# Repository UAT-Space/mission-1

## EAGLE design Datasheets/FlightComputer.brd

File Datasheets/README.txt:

Flight Computer Module [By Kenneth Vorseth]
>>For UAT SPACE Program

FlightComputer.brd : Eagle Circuit Board File
FlightComputer.sch : Eagle Schematic (VERY USEFUL!)

Temperature Rating: -40C to 85C (CPU: -40C to 105C)

Microcontroller Pinout Connections
---------------------------------------------
AVR	|    Arduino	|	Usage       |
---------------------------------------------
PD0	|	0	| UART RX   (GPS/PC)|
PD1	|	1	| UART TX   (GPS/PC)|
PD2	|	2	| 1Hz Interrupt     |
PD3	|	3	| Servo A	    |
PD5	|	5	| Servo B	    |
PD6	|	6	| Servo C	    |
PD7	|	7	| SOFT RX (RADIO RX)|
PB0	|	8	| SOFT TX (RADIO TX)|
PB2	|	10	| SS   (ISP/SD CARD)|
PB3	|	11	| MOSI (ISP/SD CARD)|
PB4	|	12	| MISO (ISP/SD CARD)|
PB5	|	13	| SCK  (ISP/SD CARD)|
PC0	|	14/A0	| GPIO A	    |
PC1	|	15/A1	| GPIO B            |
PC2	|	16/A2	| GPIO C  	    |
PC4	|	18	| SDA       (BNO055)| 
PC5	|	19	| SCL	    (BNO055)|
---------------------------------------------

Usage Notes:
- Arduino Bootloader needs to be programmed via provided ISP header.
- When programming the device, use an FTDI cable attached to the designated pinout.
	-> Note that external power (VIN) must be supplied, and the PC must share GND.
	-> This means that you CANNNOT USE A LAPTOP BATTERY, PLUG IN LAPTOP.
- Power Supply (VIN) needs to be greater than 9 Volts.
- Do NOT power manually the 5V or 3.3V rails.
- The uBlox MAX8 GPS should interrupt the MCU once every second (1Hz).
	-> This can be used as an internal timekeeping method.
- The Micro SD Card is hooked up via SPI.
- The Inertial Measurement Unit (BNO055) is hooked up via I2C.
	-> The default address for the BNO055 is in the datasheet.
- Using the two jumpers, you can swap between using the UART with...
	-> Left Position:  UART TO GPS (For use in Field)
	-> Right Position: UART TO PC (FTDI for Programming/Serial Monitor)
- The RS-232 serial port is 12V tolerant, do NOT try to use 5V on this!

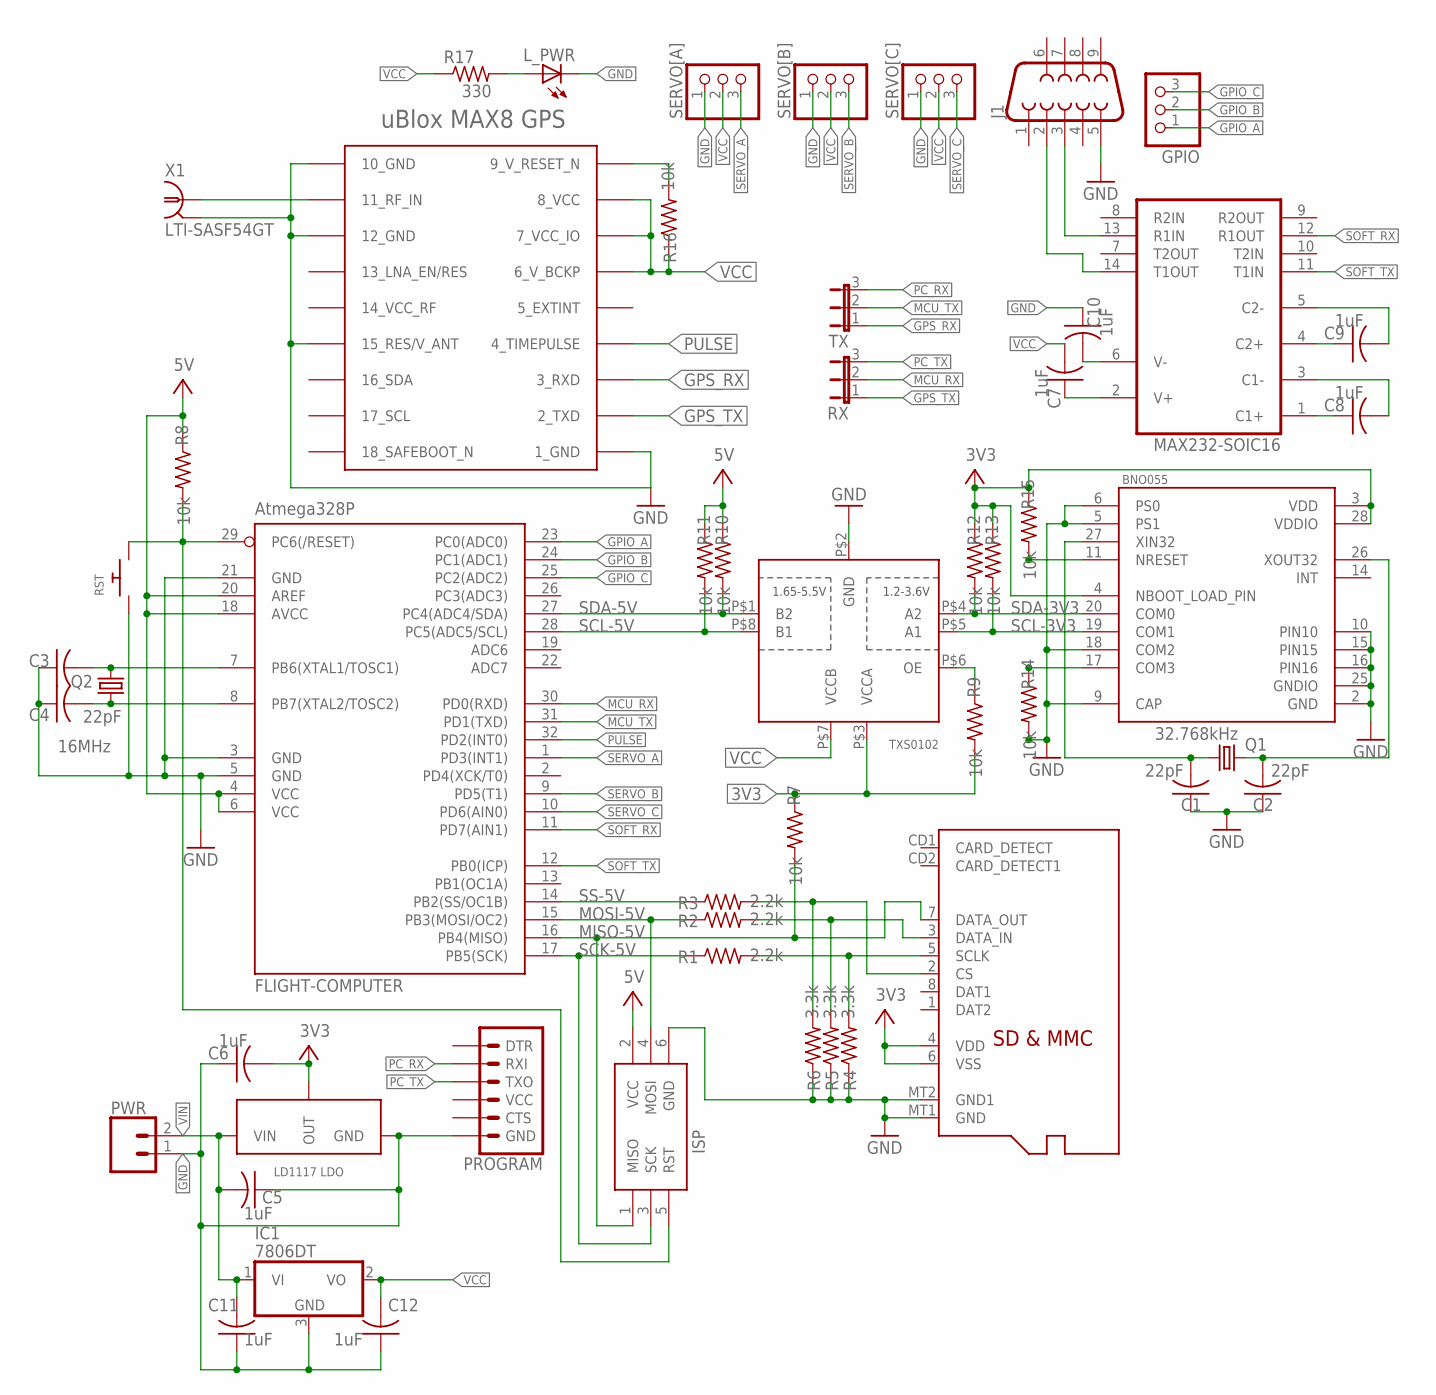
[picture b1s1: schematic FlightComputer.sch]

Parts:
BNO055: BNO055; LGA28R50P4X10_380X520X100
C1, C2, C3, C4: 22pF; C0805
C5, C6, C7, C8, C9, C10, C11, C12: 1uF; C0805
FLIGHT-COMPUTER: Atmega328P; TQFP32-08
GPIO: PINHD-1X3; 1X03
IC1: 7806DT; TO252
ISP: AVRISP-BOX
J1: DB9MALE; DB9_MALE
L_PWR: LEDSML0805; SML0805
MAX232-SOIC16: MAX232ECWE; SO16L
PROGRAM: 6_PIN_SERIAL_TARGETSILK; 6_PIN_SERIAL_TARGET_SIDE_W_SILK
PWR: CONN_02; 1X02
Q1: 32.768kHz; HC49/S
Q2: 16MHz; HC49/S
R1, R2, R3: 2.2k; R0805
R4, R5, R6: 3.3k; R0805
R7, R8, R9, R10, R11, R12, R13, R14, R15, R16: 10k; R0805
R17: 330; R0805
RST: SWITCH_PUSHBUTTONEVQ-PE; TACT_PANA-EVQ
RX: JP2E; JP2
SD-CARD: MICROSD
SERVO[A]: PINHD-1X3; 1X03
SERVO[B]: PINHD-1X3; 1X03
SERVO[C]: PINHD-1X3; 1X03
TX: JP2E; JP2
TXS0102: TXS0102; VFSOP-8
U$1: MAX-M8
U$2: LD1117
X1: LTI-SASF54GT

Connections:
3V3: BNO055.3 (VDD), BNO055.4 (NBOOT_LOAD_PIN), BNO055.28 (VDDIO), C6.2, R7.1, R9.2, R12.1, R13.1, R15.1, SD-CARD.4 (VDD), SD-CARD.6 (VSS), TXS0102.P$3 (VCCA), U$2.OUT, U$2.PAD (OUT)
BNO_RST_3V3: BNO055.11 (NRESET), R15.2
GND: BNO055.2 (GND), BNO055.5 (PS1), BNO055.6 (PS0), BNO055.9 (CAP), BNO055.10 (PIN10), BNO055.15 (PIN15), BNO055.16 (PIN16), BNO055.18 (COM2), BNO055.25 (GNDIO), C1.1, C2.1, C3.1, C4.1, C5.1, C6.1, C10.1, C11.1, C12.1, FLIGHT-COMPUTER.3 (GND), FLIGHT-COMPUTER.5 (GND), FLIGHT-COMPUTER.21 (GND), IC1.3 (GND), ISP.6 (GND), J1.5, L_PWR.C, MAX232-SOIC16.15 (GND), PROGRAM.P$6 (GND), PWR.1, R4.1, R5.1, R6.1, R14.2, RST.P$1, SD-CARD.MT1 (GND), SD-CARD.MT2 (GND1), SERVO[A].1, SERVO[B].1, SERVO[C].1, TXS0102.P$2 (GND), U$2.GND
GPIO_A: FLIGHT-COMPUTER.23 (PC0(ADC0)), GPIO.1
GPIO_B: FLIGHT-COMPUTER.24 (PC1(ADC1)), GPIO.2
GPIO_C: FLIGHT-COMPUTER.25 (PC2(ADC2)), GPIO.3
GPS_RX: TX.1, U$1.3_RXD
GPS_TX: RX.1, U$1.2_TXD
MCU_RX: FLIGHT-COMPUTER.30 (PD0(RXD)), RX.2
MCU_TX: FLIGHT-COMPUTER.31 (PD1(TXD)), TX.2
MISO-5V: FLIGHT-COMPUTER.16 (PB4(MISO)), ISP.1 (MISO), R7.2, SD-CARD.7 (DATA_OUT)
MOSI-5V: FLIGHT-COMPUTER.15 (PB3(MOSI/OC2)), ISP.4 (MOSI), R2.1
unnamed: C4.2, FLIGHT-COMPUTER.8 (PB7(XTAL2/TOSC2)), Q2.1
unnamed: C3.2, FLIGHT-COMPUTER.7 (PB6(XTAL1/TOSC1)), Q2.2
unnamed: R9.1, TXS0102.P$6 (OE)
unnamed: U$1.11_RF_IN, X1.1
unnamed: BNO055.17 (COM3), R14.1
unnamed: BNO055.27 (XIN32), C1.2, Q1.1
unnamed: R16.2, U$1.9_RESET_N (9_V_RESET_N)
unnamed: FLIGHT-COMPUTER.29 (PC6(/RESET)), ISP.5 (RST), R8.2, RST.P$2
unnamed: BNO055.26 (XOUT32), C2.2, Q1.2
unnamed: J1.3, MAX232-SOIC16.13 (R1IN)
unnamed: U$1.1_GND, U$1.10_GND, U$1.12_GND, U$1.15_V_ANT/RESERVED (15_RES/V_ANT), X1.2, X1.3 (2), X1.4 (2), X1.5 (2)
unnamed: J1.2, MAX232-SOIC16.14 (T1OUT)
unnamed: L_PWR.A, R17.2
unnamed: C7.1, MAX232-SOIC16.2 (V+)
unnamed: C8.1, MAX232-SOIC16.1 (C1+)
unnamed: C8.2, MAX232-SOIC16.3 (C1-)
unnamed: C9.1, MAX232-SOIC16.4 (C2+)
unnamed: C9.2, MAX232-SOIC16.5 (C2-)
unnamed: C10.2, MAX232-SOIC16.6 (V-)
PC_RX: PROGRAM.P$3 (RXI), TX.3
PC_TX: PROGRAM.P$2 (TXO), RX.3
PULSE: FLIGHT-COMPUTER.32 (PD2(INT0)), U$1.4_TIMEPULSE
SCK-5V: FLIGHT-COMPUTER.17 (PB5(SCK)), ISP.3 (SCK), R1.1
SCL-3V3: BNO055.19 (COM1), R13.2, TXS0102.P$5 (A1)
SCL-5V: FLIGHT-COMPUTER.28 (PC5(ADC5/SCL)), R11.2, TXS0102.P$8 (B1)
SDA-3V3: BNO055.20 (COM0), R12.2, TXS0102.P$4 (A2)
SDA-5V: FLIGHT-COMPUTER.27 (PC4(ADC4/SDA)), R10.2, TXS0102.P$1 (B2)
SD_CS: R3.2, R6.2, SD-CARD.2 (CS)
SD_MOSI: R2.2, R5.2, SD-CARD.3 (DATA_IN)
SD_SCK: R1.2, R4.2, SD-CARD.5 (SCLK)
SERVO_A: FLIGHT-COMPUTER.1 (PD3(INT1)), SERVO[A].3
SERVO_B: FLIGHT-COMPUTER.9 (PD5(T1)), SERVO[B].3
SERVO_C: FLIGHT-COMPUTER.10 (PD6(AIN0)), SERVO[C].3
SOFT_RX: FLIGHT-COMPUTER.11 (PD7(AIN1)), MAX232-SOIC16.12 (R1OUT)
SOFT_TX: FLIGHT-COMPUTER.12 (PB0(ICP)), MAX232-SOIC16.11 (T1IN)
SS-5V: FLIGHT-COMPUTER.14 (PB2(SS/OC1B)), R3.1
VCC: C7.2, C12.2, FLIGHT-COMPUTER.4 (VCC), FLIGHT-COMPUTER.6 (VCC), FLIGHT-COMPUTER.18 (AVCC), FLIGHT-COMPUTER.20 (AREF), IC1.2 (VO), ISP.2 (VCC), MAX232-SOIC16.16 (VCC), R8.1, R10.1, R11.1, R16.1, R17.1, SERVO[A].2, SERVO[B].2, SERVO[C].2, TXS0102.P$7 (VCCB), U$1.6_V_BCKP, U$1.7_VCC_IO, U$1.8_VCC
VIN: C5.2, C11.2, IC1.1 (VI), PWR.2, U$2.IN (VIN)

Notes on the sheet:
uBlox MAX8 GPS

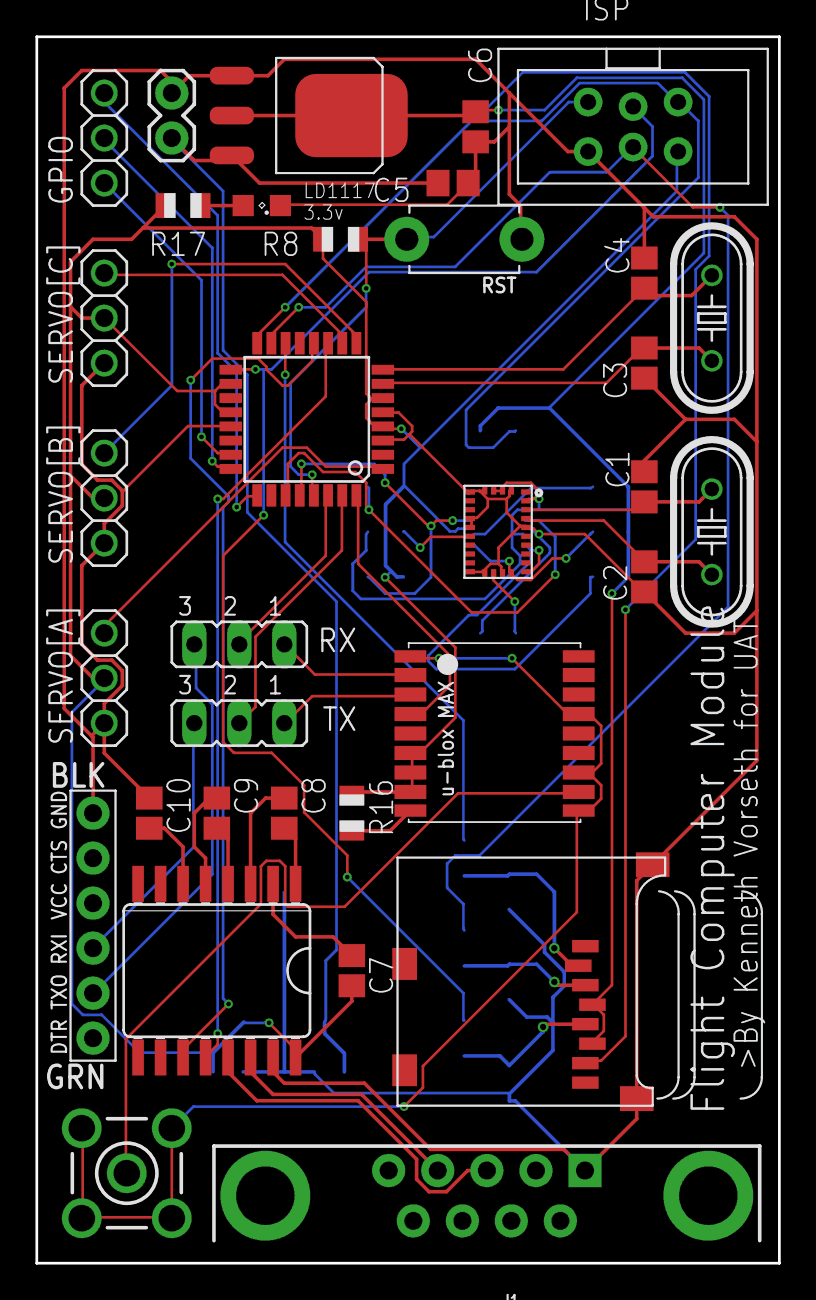
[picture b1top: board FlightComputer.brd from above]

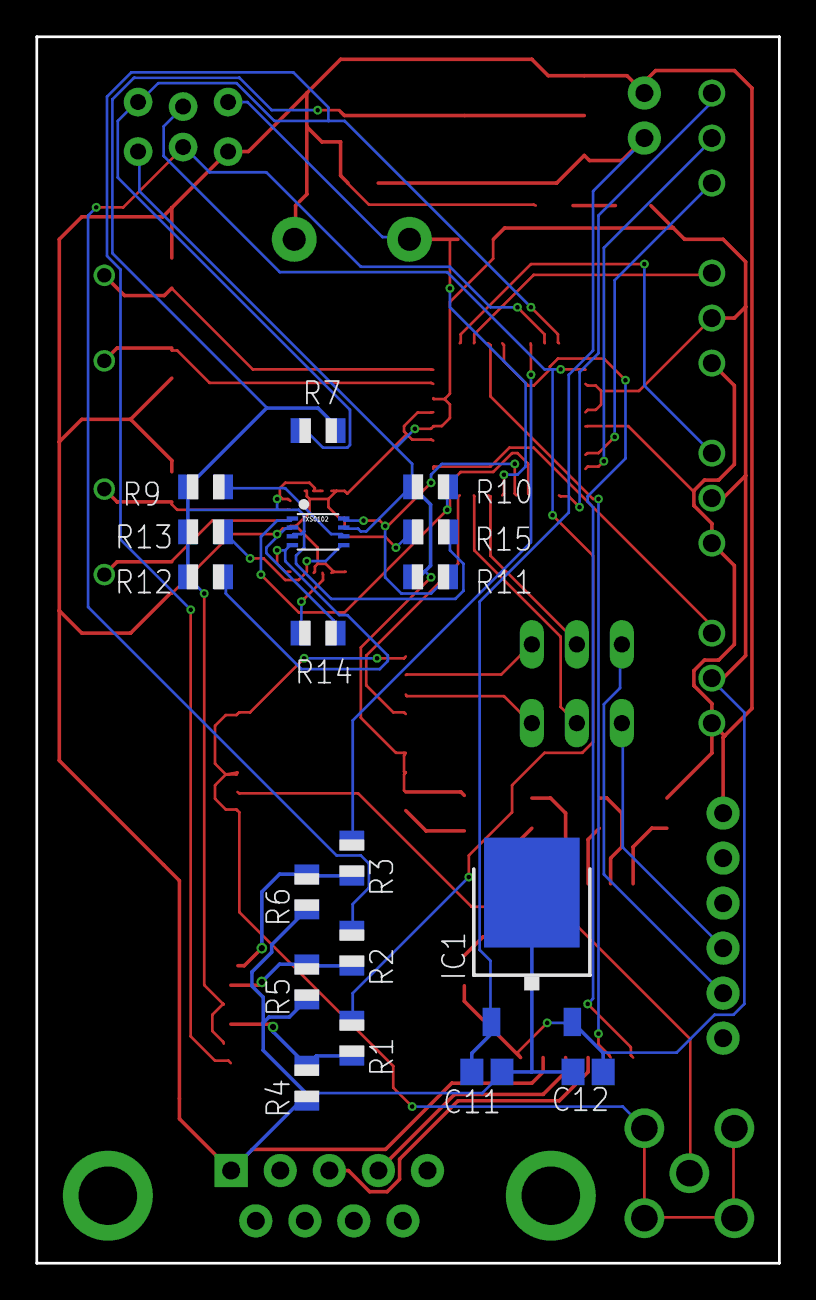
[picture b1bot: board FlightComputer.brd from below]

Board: 2 copper layers, 41.9 x 69.2 mm, 52 parts (18 on the bottom side), 50 nets.

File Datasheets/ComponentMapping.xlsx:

| Resistors (Case Code 805) |  |  |  | Capacitors (Case Code 805)
 | Component# | Value | Description |  | Component# | Value | Description
 | R1 | 2.2k | SCK Voltage Divider |  | C1 | 22pF | BNO055 Osc
 | R2 | 2.2k | MOSI Voltage Divider |  | C2 | 22pF | BNO055 Osc
 | R3 | 2.2k | SS Voltage Divider |  | C3 | 22pF | AVR Osc
 | R4 | 3.3k | SCK Voltage Divider |  | C4 | 22pF | AVR Osc
 | R5 | 3.3k | MOSI Voltage Divider |  | C5 | 1uF | 3v3 Regulator
 | R6 | 3.3k | SS Voltage Divider |  | C6 | 1uF | 3v3 Regulator
 | R7 | 10k | MISO Pullup 3V3 |  | C7 | 1uF | MAX232
 | R8 | 10k | AVR RST Pullup 5V |  | C8 | 1uF | MAX232
 | R9 | 10k | Shifter OE Pullup 3V3 |  | C9 | 1uF | MAX232
 | R10 | 10k | Shifter B2 Pullup 5V |  | C10 | 1uF | MAX232
 | R11 | 10k | Shifter B1 Pullup 5V |  | C11 | 1uF | 5v Regulator
 | R12 | 10k | Shifter A2 Pullup 3V3 |  | C12 | 1uF | 5v Regulator
 | R13 | 10k | Shifter A1 Pullup 3V3
 | R14 | 10k | BNO055 Pulldown |  | Connectors (Various)
 | R15 | 10k | BNO055 RST Pullup 3V3 |  | SMA Antenna (50ohm) : Male
 | R16 | 10k | Max8 RST Pullup 5V |  | DB9 RS232 : Female
 | R17 | 330 | PWR LED Limiter |  | SD Card Slot
 | Integrated Circuits |  |  |  | Other Components
 | Component# | Description |  |  | Crystal Oscillator (32.768kHz) [Radial]
 | Atmega328P | AVR Microcontroller [QFP] |  |  | Crystal Oscillator (16MHz) [Radial]
 | LD1117 LDO | 3V3 Voltage Regulator |  |  | 5V Rated LED [Case Code 805]
 | 7805 LDO | 5V Voltage Regulator |  |  | SMA Antenna Tuned for GPS
 | TXS0102 | 2 Bit Level Bidirectional Level Shifter
 | BNO055 | Inertial Measurement Unit
 | MAX232 | RS-232 to UART Converter [SOIC-16]
 | uBlox MAX8 | GPS Unit [Check Grade]

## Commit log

2019-01-20 Initial Upload

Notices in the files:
parts and their libraries:
SparkFun-Connectors: Licensing: Creative Commons ShareAlike 4.0 International - https://creativecommons.org/licenses/by-sa/4.0
